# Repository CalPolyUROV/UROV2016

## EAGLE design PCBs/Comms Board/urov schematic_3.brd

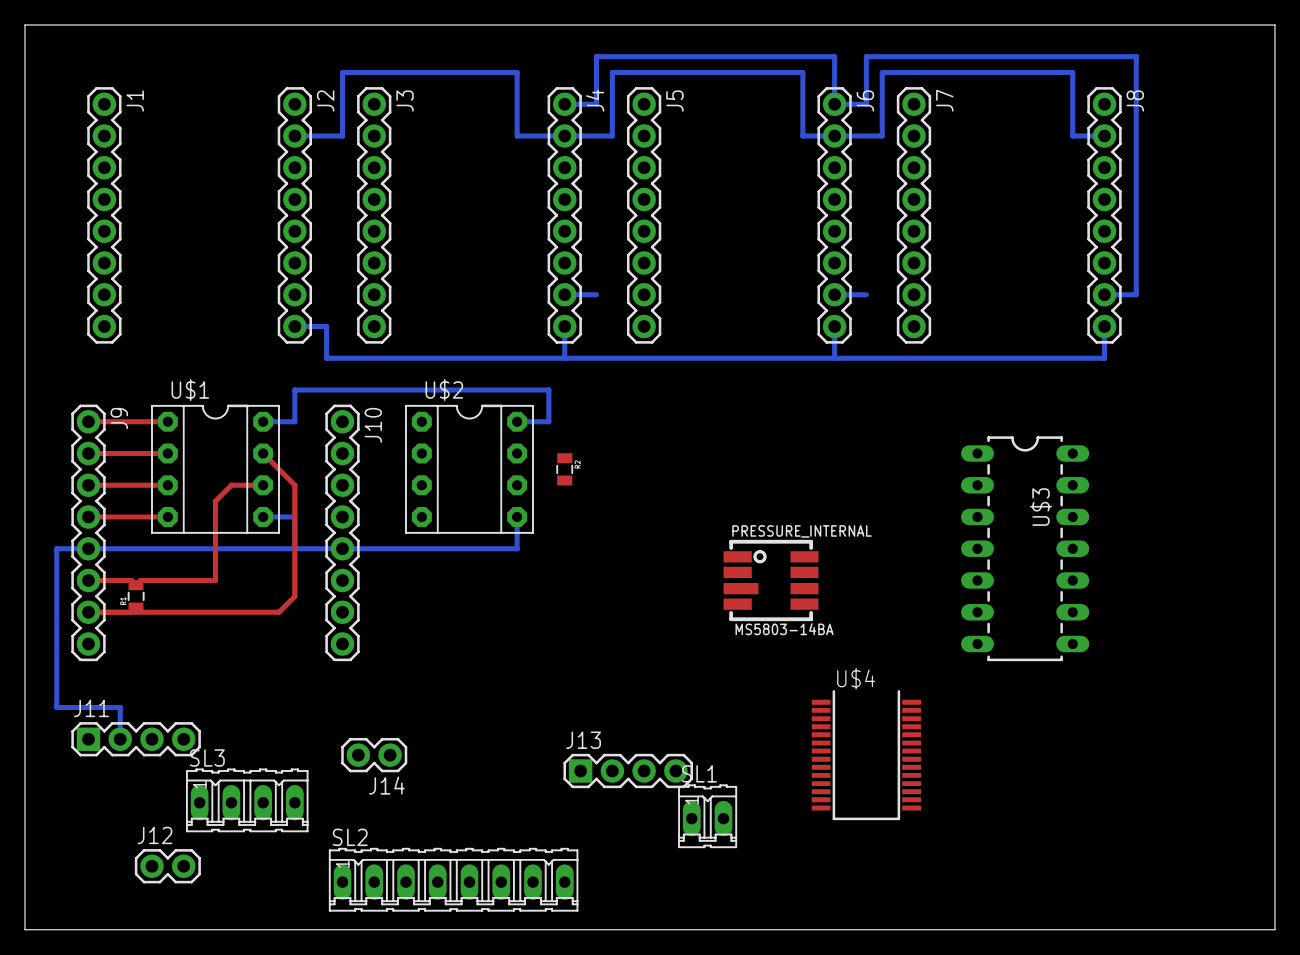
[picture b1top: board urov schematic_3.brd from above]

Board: 2 copper layers, 100.0 x 72.4 mm, 24 parts (0 on the bottom side), 21 nets.

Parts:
J1, J2, J3, J4, J5, J6, J7, J8, J9, J10: 1X08_ROUND
J11, J13: 1X04
J12, J14: 1X02
PRESSURE_INTERNAL: MS5803-14BA; MS5803
R1, R2: 120; 0805
SL1: 02P
SL2: 08P
SL3: 04P
U$1, U$2: MAX485DIL; DIL08
U$3: ATTINY84ATTINY84-20PU; DIL14
U$4: MAX4574A; 28-SSOP

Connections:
A_DIP8_1: J9.6, R1.2, U$1.6
A_DIP8_2: J10.6, R2.2, U$2.6
B_DIP8_1: J9.7, R1.1, U$1.7
B_DIP8_2: J10.7, R2.1, U$2.7
GND: J2.1, J2.7, J4.1, J4.7, J6.1, J6.7, J8.1, J8.7, J9.5, J10.5, J11.2, PRESSURE_INTERNAL.2, PRESSURE_INTERNAL.6, U$1.5, U$2.5
MISO: J13.3, PRESSURE_INTERNAL.8
MOSI: J12.1, J13.4, PRESSURE_INTERNAL.7
unnamed: J9.1, U$1.1
unnamed: J9.2, U$1.2
unnamed: J9.3, U$1.3
unnamed: J9.4, U$1.4
unnamed: J10.1, U$2.1
unnamed: J10.2, U$2.2
unnamed: J10.3, U$2.3
unnamed: J10.4, U$2.4
SCL: J11.4, J14.2, PRESSURE_INTERNAL.1
SCLK: J13.2, J14.1
SDA: J11.3, J12.2
SS: J13.1, PRESSURE_INTERNAL.3
VDD: J2.2, J4.2, J6.2, J8.2, J9.8, J10.8, U$1.8, U$2.8
VMOT: J2.8, J4.8, J6.8, J8.8

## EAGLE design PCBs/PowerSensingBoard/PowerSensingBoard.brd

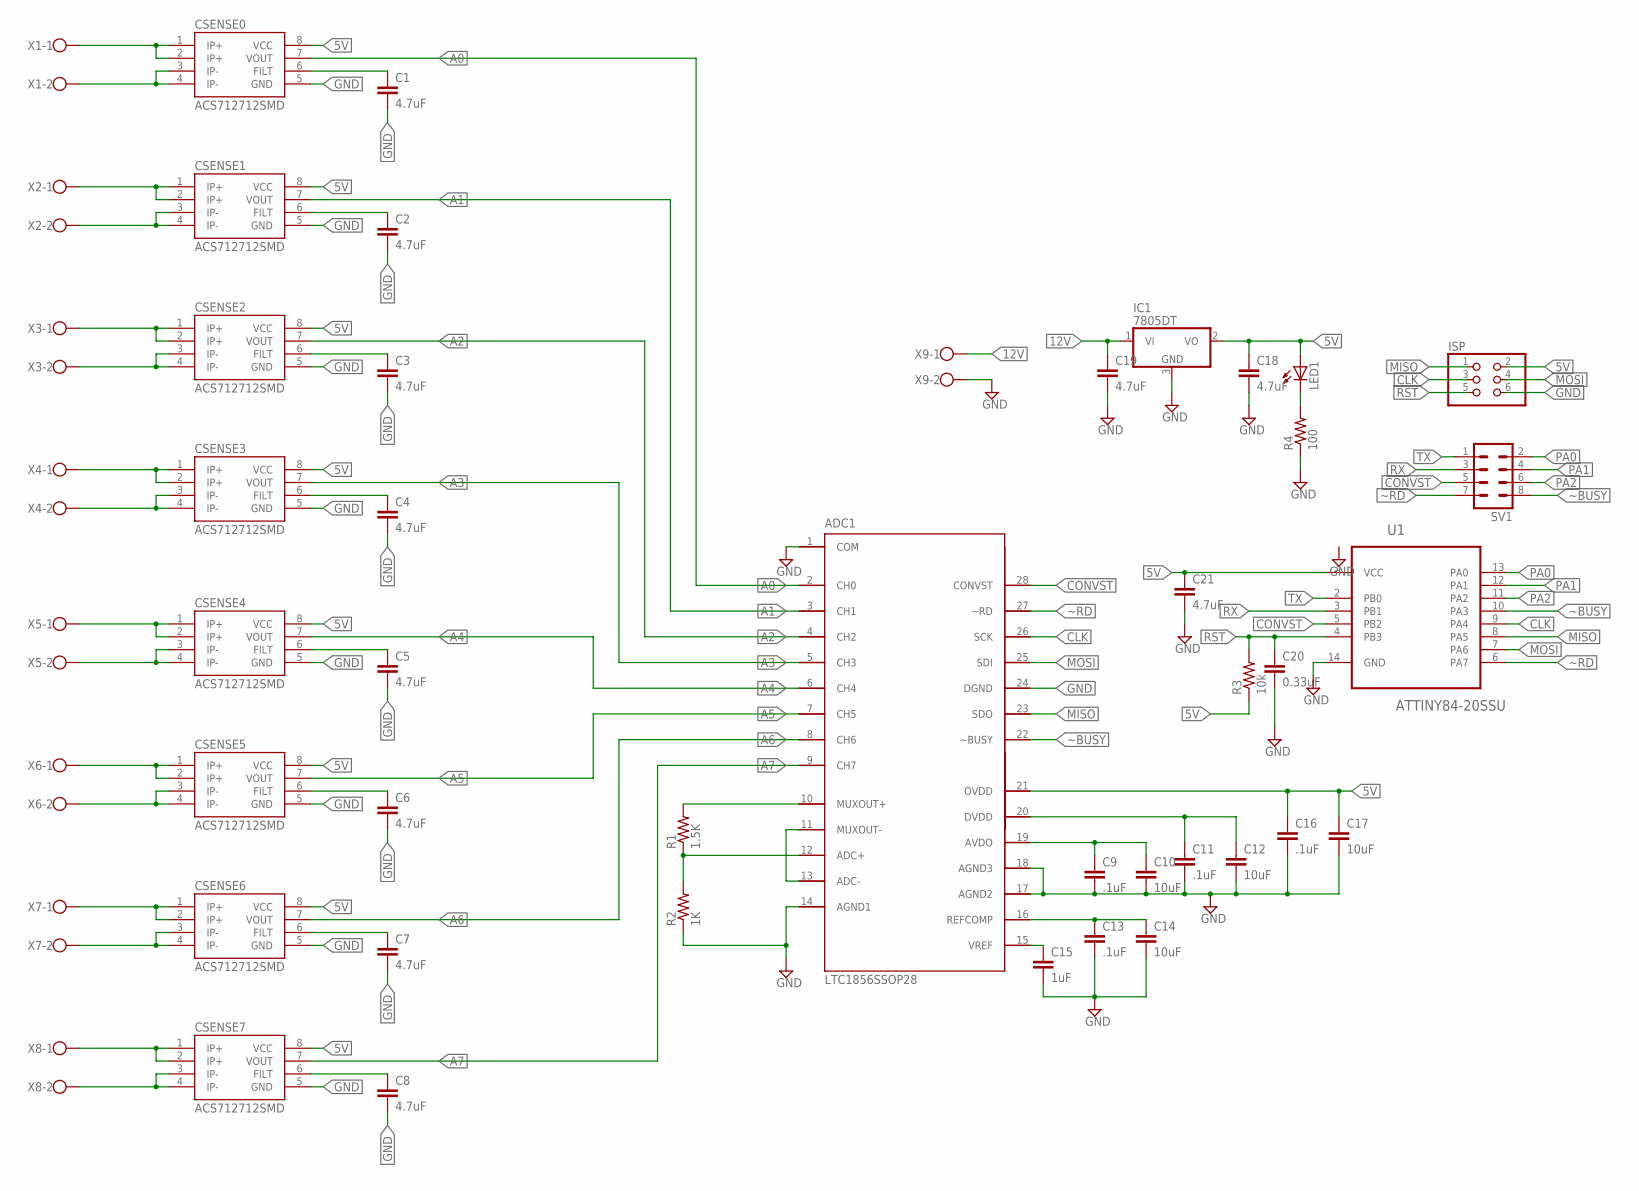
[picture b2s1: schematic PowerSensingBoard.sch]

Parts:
ADC1: LTC1856SSOP28; SSOP-28
C1, C2, C3, C4, C5, C6, C7, C8, C18, C19, C21: 4.7uF; 0603-CAP
C9, C11, C13, C16: .1uF; 0603-CAP
C10, C12, C14, C17: 10uF; 0603-CAP
C15: 1uF; 0603-CAP
C20: 0.33uF; 0805-CAP
CSENSE0, CSENSE1, CSENSE2, CSENSE3, CSENSE4, CSENSE5, CSENSE6, CSENSE7: ACS712712SMD; SO08
IC1: 7805DT; TO252
ISP: PINHD-2X3; 2X03
LED1: LEDCHIP-LED0805; CHIP-LED0805
R1: 1.5K; 0603-RES
R2: 1K; 0603-RES
R3: 10k; 0805
R4: 100; 0603-RES
SV1: MA04-2
U1: ATTINY84-20SSU; SOIC127P600X175-14N
X1, X2, X3, X4, X5, X6, X7, X8, X9: W237-102

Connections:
5V: ADC1.21 (OVDD), C16.1, C17.1, C18.1, C21.1, CSENSE0.8 (VCC), CSENSE1.8 (VCC), CSENSE2.8 (VCC), CSENSE3.8 (VCC), CSENSE4.8 (VCC), CSENSE5.8 (VCC), CSENSE6.8 (VCC), CSENSE7.8 (VCC), IC1.2 (VO), ISP.2, LED1.A, R3.1, U1.1 (VCC)
12V: C19.1, IC1.1 (VI), X9.1
A0: ADC1.2 (CH0), CSENSE0.7 (VOUT)
A1: ADC1.3 (CH1), CSENSE1.7 (VOUT)
A2: ADC1.4 (CH2), CSENSE2.7 (VOUT)
A3: ADC1.5 (CH3), CSENSE3.7 (VOUT)
A4: ADC1.6 (CH4), CSENSE4.7 (VOUT)
A5: ADC1.7 (CH5), CSENSE5.7 (VOUT)
A6: ADC1.8 (CH6), CSENSE6.7 (VOUT)
A7: ADC1.9 (CH7), CSENSE7.7 (VOUT)
CLK: ADC1.26 (SCK), ISP.3, U1.9 (PA4)
CONVST: ADC1.28 (CONVST), SV1.5, U1.5 (PB2)
FILT1: C1.1, CSENSE0.6 (FILT)
FILT2: C2.1, CSENSE1.6 (FILT)
FILT3: C3.1, CSENSE2.6 (FILT)
FILT4: C4.1, CSENSE3.6 (FILT)
FILT5: C5.1, CSENSE4.6 (FILT)
FILT6: C6.1, CSENSE5.6 (FILT)
FILT7: C7.1, CSENSE6.6 (FILT)
FILT8: C8.1, CSENSE7.6 (FILT)
GND: ADC1.1 (COM), ADC1.14 (AGND1), ADC1.17 (AGND2), ADC1.18 (AGND3), ADC1.24 (DGND), C1.2, C2.2, C3.2, C4.2, C5.2, C6.2, C7.2, C8.2, C9.2, C10.2, C11.2, C12.2, C13.2, C14.2, C15.2, C16.2, C17.2, C18.2, C19.2, C20.2, C21.2, CSENSE0.5 (GND), CSENSE1.5 (GND), CSENSE2.5 (GND), CSENSE3.5 (GND), CSENSE4.5 (GND), CSENSE5.5 (GND), CSENSE6.5 (GND), CSENSE7.5 (GND), IC1.3 (GND), ISP.6, R2.1, R4.1, U1.14 (GND), X9.2
INT1: CSENSE0.1 (IP+), CSENSE0.2 (IP+), X1.1
INT2: CSENSE1.1 (IP+), CSENSE1.2 (IP+), X2.1
INT3: CSENSE2.1 (IP+), CSENSE2.2 (IP+), X3.1
INT4: CSENSE3.1 (IP+), CSENSE3.2 (IP+), X4.1
INT5: CSENSE4.1 (IP+), CSENSE4.2 (IP+), X5.1
INT6: CSENSE5.1 (IP+), CSENSE5.2 (IP+), X6.1
INT7: CSENSE6.1 (IP+), CSENSE6.2 (IP+), X7.1
INT8: CSENSE7.1 (IP+), CSENSE7.2 (IP+), X8.1
LED1: LED1.C, R4.2
MISO: ADC1.23 (SDO), ISP.1, U1.8 (PA5)
MOSI: ADC1.25 (SDI), ISP.4, U1.7 (PA6)
MUXOUT+: ADC1.10 (MUXOUT+), R1.2
MUXOUT-: ADC1.12 (ADC+), R1.1, R2.2
unnamed: ADC1.11 (MUXOUT-), ADC1.13 (ADC-)
unnamed: ADC1.20 (DVDD), C11.1, C12.1
unnamed: ADC1.19 (AVDO), C9.1, C10.1
unnamed: ADC1.15 (VREF), C15.1
unnamed: ADC1.16 (REFCOMP), C13.1, C14.1
OUTT1: CSENSE0.3 (IP-), CSENSE0.4 (IP-), X1.2
OUTT2: CSENSE1.3 (IP-), CSENSE1.4 (IP-), X2.2
OUTT3: CSENSE2.3 (IP-), CSENSE2.4 (IP-), X3.2
OUTT4: CSENSE3.3 (IP-), CSENSE3.4 (IP-), X4.2
OUTT5: CSENSE4.3 (IP-), CSENSE4.4 (IP-), X5.2
OUTT6: CSENSE5.3 (IP-), CSENSE5.4 (IP-), X6.2
OUTT7: CSENSE6.3 (IP-), CSENSE6.4 (IP-), X7.2
OUTT8: CSENSE7.3 (IP-), CSENSE7.4 (IP-), X8.2
PA0: SV1.2, U1.13 (PA0)
PA1: SV1.4, U1.12 (PA1)
PA2: SV1.6, U1.11 (PA2)
RST: C20.1, ISP.5, R3.2, U1.4 (PB3)
RX: SV1.3, U1.3 (PB1)
TX: SV1.1, U1.2 (PB0)
~BUSY: ADC1.22 (~BUSY), SV1.8, U1.10 (PA3)
~RD: ADC1.27 (~RD), SV1.7, U1.6 (PA7)

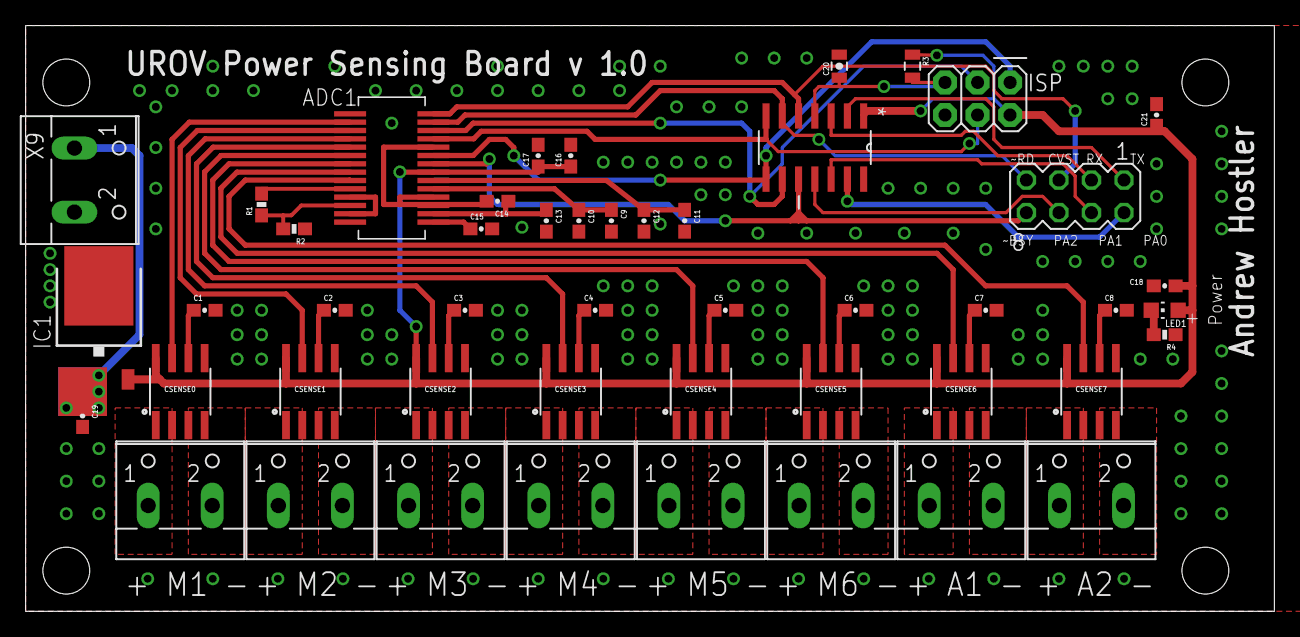
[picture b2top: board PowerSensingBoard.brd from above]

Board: 2 copper layers, 97.5 x 45.7 mm, 48 parts (0 on the bottom side), 55 nets.

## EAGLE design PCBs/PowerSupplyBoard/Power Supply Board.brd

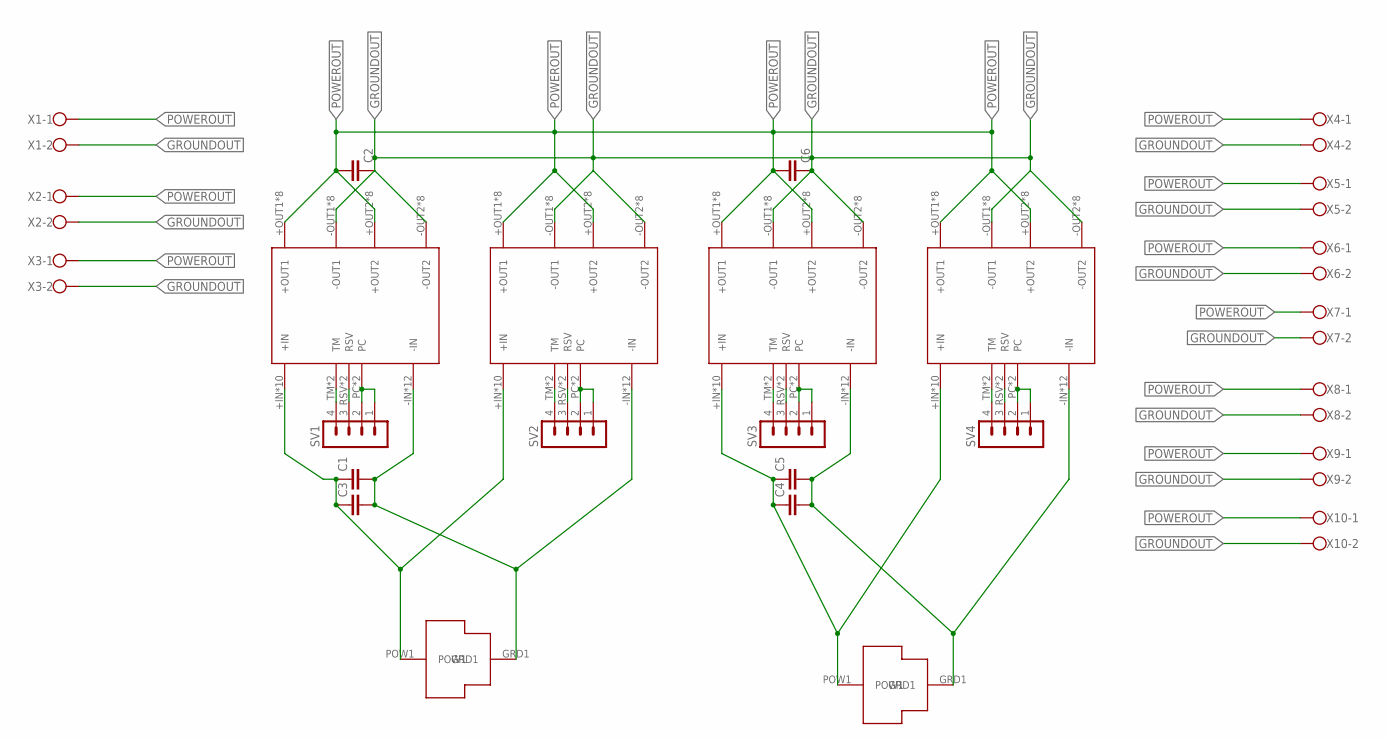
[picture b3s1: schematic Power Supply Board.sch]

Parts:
C1, C2, C3, C4, C5, C6: C2,5-3; C2.5-3
SV1, SV2, SV3, SV4: MA04-1
U$3, U$9: MOLEXMEGAFIT
VC1, VC2, VC3, VC4: VOLTAGECONVERTER
X1, X2, X3, X4, X5, X6, X7, X8, X9, X10: W237-102

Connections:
GROUNDIN: C1.2, C3.2, C4.2, C5.2, U$3.GRD1, U$9.GRD1, VC1.-IN, VC1.-IN@0 (-IN), VC1.-IN@1 (-IN), VC1.-IN@2 (-IN), VC1.-IN@3 (-IN), VC1.-IN@4 (-IN), VC1.-IN@5 (-IN), VC1.-IN@6 (-IN), VC1.-IN@7 (-IN), VC1.-IN@8 (-IN), VC1.-IN@9 (-IN), VC1.-IN@10 (-IN), VC2.-IN, VC2.-IN@0 (-IN), VC2.-IN@1 (-IN), VC2.-IN@2 (-IN), VC2.-IN@3 (-IN), VC2.-IN@4 (-IN), VC2.-IN@5 (-IN), VC2.-IN@6 (-IN), VC2.-IN@7 (-IN), VC2.-IN@8 (-IN), VC2.-IN@9 (-IN), VC2.-IN@10 (-IN), VC3.-IN, VC3.-IN@0 (-IN), VC3.-IN@1 (-IN), VC3.-IN@2 (-IN), VC3.-IN@3 (-IN), VC3.-IN@4 (-IN), VC3.-IN@5 (-IN), VC3.-IN@6 (-IN), VC3.-IN@7 (-IN), VC3.-IN@8 (-IN), VC3.-IN@9 (-IN), VC3.-IN@10 (-IN), VC4.-IN, VC4.-IN@0 (-IN), VC4.-IN@1 (-IN), VC4.-IN@2 (-IN), VC4.-IN@3 (-IN), VC4.-IN@4 (-IN), VC4.-IN@5 (-IN), VC4.-IN@6 (-IN), VC4.-IN@7 (-IN), VC4.-IN@8 (-IN), VC4.-IN@9 (-IN), VC4.-IN@10 (-IN)
GROUNDOUT: C2.1, C6.1, VC1.-OUT1, VC1.-OUT1@1 (-OUT1), VC1.-OUT1@2 (-OUT1), VC1.-OUT1@3 (-OUT1), VC1.-OUT1@4 (-OUT1), VC1.-OUT1@5 (-OUT1), VC1.-OUT1@6 (-OUT1), VC1.-OUT1@7 (-OUT1), VC1.-OUT2, VC1.-OUT2@1 (-OUT2), VC1.-OUT2@2 (-OUT2), VC1.-OUT2@3 (-OUT2), VC1.-OUT2@4 (-OUT2), VC1.-OUT2@5 (-OUT2), VC1.-OUT2@6 (-OUT2), VC1.-OUT2@7 (-OUT2), VC2.-OUT1, VC2.-OUT1@1 (-OUT1), VC2.-OUT1@2 (-OUT1), VC2.-OUT1@3 (-OUT1), VC2.-OUT1@4 (-OUT1), VC2.-OUT1@5 (-OUT1), VC2.-OUT1@6 (-OUT1), VC2.-OUT1@7 (-OUT1), VC2.-OUT2, VC2.-OUT2@1 (-OUT2), VC2.-OUT2@2 (-OUT2), VC2.-OUT2@3 (-OUT2), VC2.-OUT2@4 (-OUT2), VC2.-OUT2@5 (-OUT2), VC2.-OUT2@6 (-OUT2), VC2.-OUT2@7 (-OUT2), VC3.-OUT1, VC3.-OUT1@1 (-OUT1), VC3.-OUT1@2 (-OUT1), VC3.-OUT1@3 (-OUT1), VC3.-OUT1@4 (-OUT1), VC3.-OUT1@5 (-OUT1), VC3.-OUT1@6 (-OUT1), VC3.-OUT1@7 (-OUT1), VC3.-OUT2, VC3.-OUT2@1 (-OUT2), VC3.-OUT2@2 (-OUT2), VC3.-OUT2@3 (-OUT2), VC3.-OUT2@4 (-OUT2), VC3.-OUT2@5 (-OUT2), VC3.-OUT2@6 (-OUT2), VC3.-OUT2@7 (-OUT2), VC4.-OUT1, VC4.-OUT1@1 (-OUT1), VC4.-OUT1@2 (-OUT1), VC4.-OUT1@3 (-OUT1), VC4.-OUT1@4 (-OUT1), VC4.-OUT1@5 (-OUT1), VC4.-OUT1@6 (-OUT1), VC4.-OUT1@7 (-OUT1), VC4.-OUT2, VC4.-OUT2@1 (-OUT2), VC4.-OUT2@2 (-OUT2), VC4.-OUT2@3 (-OUT2), VC4.-OUT2@4 (-OUT2), VC4.-OUT2@5 (-OUT2), VC4.-OUT2@6 (-OUT2), VC4.-OUT2@7 (-OUT2), X1.2, X2.2, X3.2, X4.2, X5.2, X6.2, X7.2, X8.2, X9.2, X10.2
unnamed: SV1.3, VC1.RSV, VC1.RSV@1 (RSV)
unnamed: SV2.3, VC2.RSV, VC2.RSV@1 (RSV)
unnamed: SV3.3, VC3.RSV, VC3.RSV@1 (RSV)
unnamed: SV4.3, VC4.RSV, VC4.RSV@1 (RSV)
PC1: SV1.1, SV1.2, VC1.PC, VC1.PC21 (PC)
PC2: SV2.1, SV2.2, VC2.PC, VC2.PC21 (PC)
PC3: SV3.1, SV3.2, VC3.PC, VC3.PC21 (PC)
PC4: SV4.1, SV4.2, VC4.PC, VC4.PC21 (PC)
POWERIN12: C1.1, C3.1, U$3.POW1, VC1.+IN, VC1.+IN@1 (+IN), VC1.+IN@2 (+IN), VC1.+IN@3 (+IN), VC1.+IN@4 (+IN), VC1.+IN@5 (+IN), VC1.+IN@6 (+IN), VC1.+IN@7 (+IN), VC1.+IN@8 (+IN), VC1.+IN@9 (+IN), VC2.+IN, VC2.+IN@1 (+IN), VC2.+IN@2 (+IN), VC2.+IN@3 (+IN), VC2.+IN@4 (+IN), VC2.+IN@5 (+IN), VC2.+IN@6 (+IN), VC2.+IN@7 (+IN), VC2.+IN@8 (+IN), VC2.+IN@9 (+IN)
POWERIN34: C4.1, C5.1, U$9.POW1, VC3.+IN, VC3.+IN@1 (+IN), VC3.+IN@2 (+IN), VC3.+IN@3 (+IN), VC3.+IN@4 (+IN), VC3.+IN@5 (+IN), VC3.+IN@6 (+IN), VC3.+IN@7 (+IN), VC3.+IN@8 (+IN), VC3.+IN@9 (+IN), VC4.+IN, VC4.+IN@1 (+IN), VC4.+IN@2 (+IN), VC4.+IN@3 (+IN), VC4.+IN@4 (+IN), VC4.+IN@5 (+IN), VC4.+IN@6 (+IN), VC4.+IN@7 (+IN), VC4.+IN@8 (+IN), VC4.+IN@9 (+IN)
POWEROUT: C2.2, C6.2, VC1.+OUT1, VC1.+OUT1@1 (+OUT1), VC1.+OUT1@2 (+OUT1), VC1.+OUT1@3 (+OUT1), VC1.+OUT1@4 (+OUT1), VC1.+OUT1@5 (+OUT1), VC1.+OUT1@6 (+OUT1), VC1.+OUT1@7 (+OUT1), VC1.+OUT2, VC1.+OUT2@1 (+OUT2), VC1.+OUT2@2 (+OUT2), VC1.+OUT2@3 (+OUT2), VC1.+OUT2@4 (+OUT2), VC1.+OUT2@5 (+OUT2), VC1.+OUT2@6 (+OUT2), VC1.+OUT2@7 (+OUT2), VC2.+OUT1, VC2.+OUT1@1 (+OUT1), VC2.+OUT1@2 (+OUT1), VC2.+OUT1@3 (+OUT1), VC2.+OUT1@4 (+OUT1), VC2.+OUT1@5 (+OUT1), VC2.+OUT1@6 (+OUT1), VC2.+OUT1@7 (+OUT1), VC2.+OUT2, VC2.+OUT2@1 (+OUT2), VC2.+OUT2@2 (+OUT2), VC2.+OUT2@3 (+OUT2), VC2.+OUT2@4 (+OUT2), VC2.+OUT2@5 (+OUT2), VC2.+OUT2@6 (+OUT2), VC2.+OUT2@7 (+OUT2), VC3.+OUT1, VC3.+OUT1@1 (+OUT1), VC3.+OUT1@2 (+OUT1), VC3.+OUT1@3 (+OUT1), VC3.+OUT1@4 (+OUT1), VC3.+OUT1@5 (+OUT1), VC3.+OUT1@6 (+OUT1), VC3.+OUT1@7 (+OUT1), VC3.+OUT2, VC3.+OUT2@1 (+OUT2), VC3.+OUT2@2 (+OUT2), VC3.+OUT2@3 (+OUT2), VC3.+OUT2@4 (+OUT2), VC3.+OUT2@5 (+OUT2), VC3.+OUT2@6 (+OUT2), VC3.+OUT2@7 (+OUT2), VC4.+OUT1, VC4.+OUT1@1 (+OUT1), VC4.+OUT1@2 (+OUT1), VC4.+OUT1@3 (+OUT1), VC4.+OUT1@4 (+OUT1), VC4.+OUT1@5 (+OUT1), VC4.+OUT1@6 (+OUT1), VC4.+OUT1@7 (+OUT1), VC4.+OUT2, VC4.+OUT2@1 (+OUT2), VC4.+OUT2@2 (+OUT2), VC4.+OUT2@3 (+OUT2), VC4.+OUT2@4 (+OUT2), VC4.+OUT2@5 (+OUT2), VC4.+OUT2@6 (+OUT2), VC4.+OUT2@7 (+OUT2), X1.1, X2.1, X3.1, X4.1, X5.1, X6.1, X7.1, X8.1, X9.1, X10.1
TM1: SV1.4, VC1.TM, VC1.TM@1 (TM)
TM2: SV2.4, VC2.TM, VC2.TM@1 (TM)
TM3: SV3.4, VC3.TM, VC3.TM@1 (TM)
TM4: SV4.4, VC4.TM, VC4.TM@1 (TM)

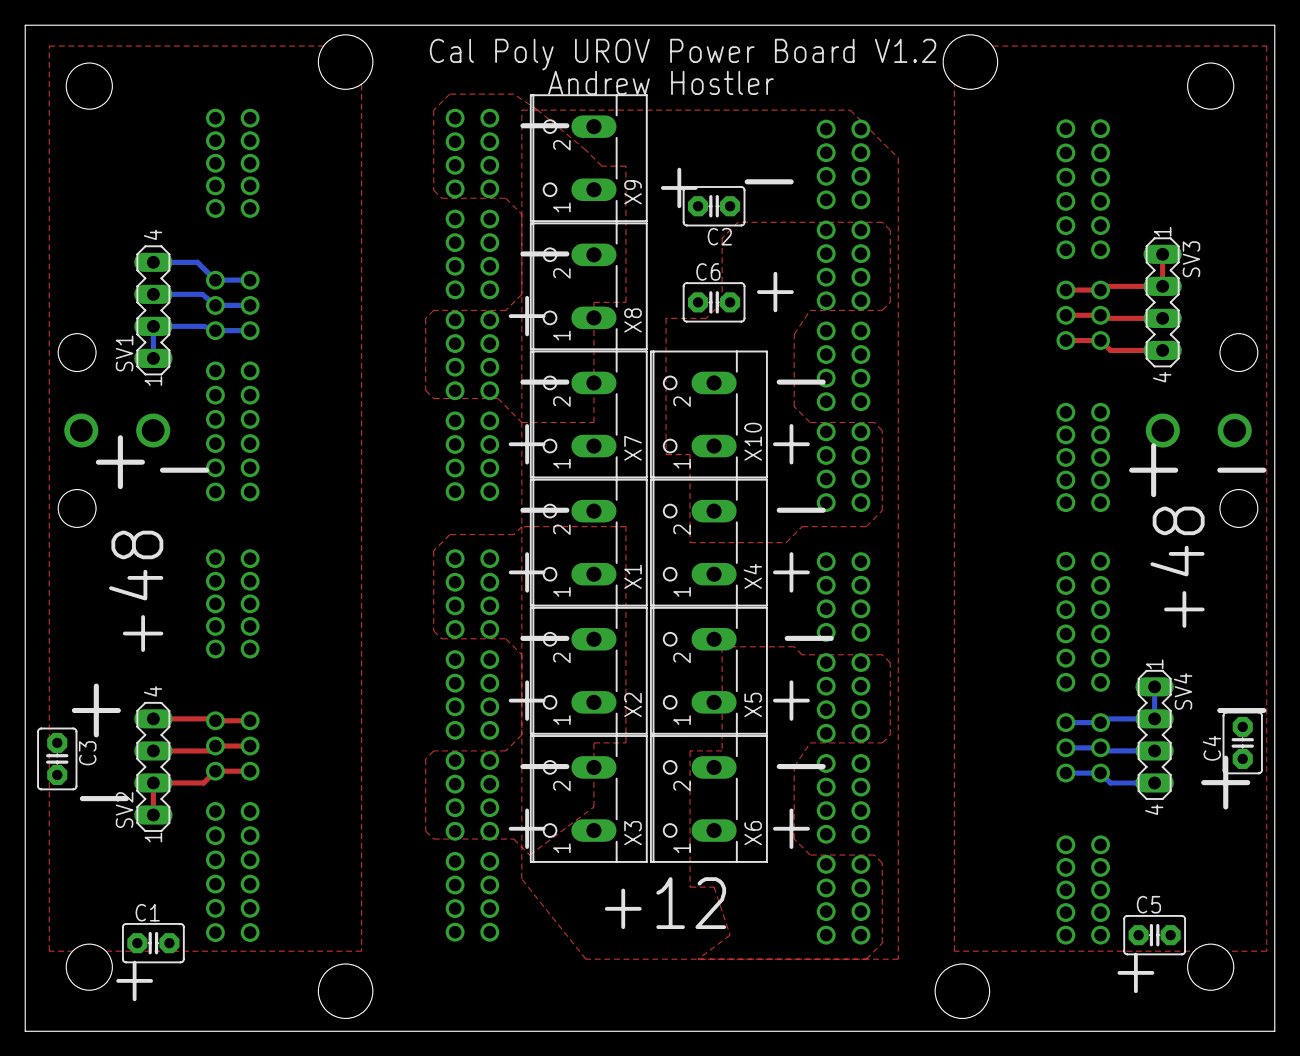
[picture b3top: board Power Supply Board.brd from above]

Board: 2 copper layers, 99.1 x 79.8 mm, 26 parts (0 on the bottom side), 17 nets.

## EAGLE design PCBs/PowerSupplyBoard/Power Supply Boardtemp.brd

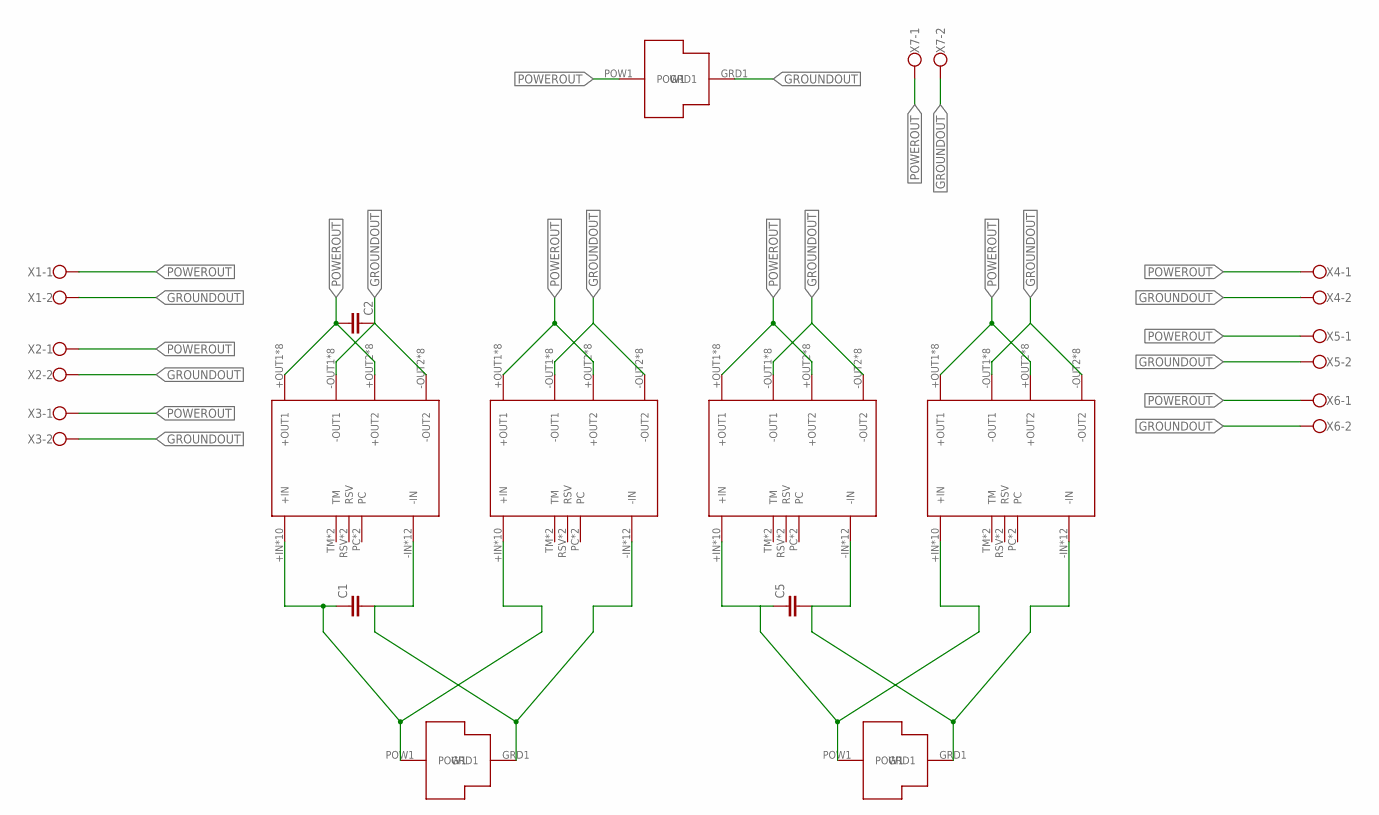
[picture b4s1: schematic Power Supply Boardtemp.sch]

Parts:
C1, C2, C5: C2,5-3; C2.5-3
U$2, U$3, U$9: MOLEXMEGAFIT
VC1, VC2, VC3, VC4: VOLTAGECONVERTER
X1, X2, X3, X4, X5, X6, X7: W237-102

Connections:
GROUNDIN: C1.2, C5.2, U$3.GRD1, U$9.GRD1, VC1.-IN, VC1.-IN@0 (-IN), VC1.-IN@1 (-IN), VC1.-IN@2 (-IN), VC1.-IN@3 (-IN), VC1.-IN@4 (-IN), VC1.-IN@5 (-IN), VC1.-IN@6 (-IN), VC1.-IN@7 (-IN), VC1.-IN@8 (-IN), VC1.-IN@9 (-IN), VC1.-IN@10 (-IN), VC2.-IN, VC2.-IN@0 (-IN), VC2.-IN@1 (-IN), VC2.-IN@2 (-IN), VC2.-IN@3 (-IN), VC2.-IN@4 (-IN), VC2.-IN@5 (-IN), VC2.-IN@6 (-IN), VC2.-IN@7 (-IN), VC2.-IN@8 (-IN), VC2.-IN@9 (-IN), VC2.-IN@10 (-IN), VC3.-IN, VC3.-IN@0 (-IN), VC3.-IN@1 (-IN), VC3.-IN@2 (-IN), VC3.-IN@3 (-IN), VC3.-IN@4 (-IN), VC3.-IN@5 (-IN), VC3.-IN@6 (-IN), VC3.-IN@7 (-IN), VC3.-IN@8 (-IN), VC3.-IN@9 (-IN), VC3.-IN@10 (-IN), VC4.-IN, VC4.-IN@0 (-IN), VC4.-IN@1 (-IN), VC4.-IN@2 (-IN), VC4.-IN@3 (-IN), VC4.-IN@4 (-IN), VC4.-IN@5 (-IN), VC4.-IN@6 (-IN), VC4.-IN@7 (-IN), VC4.-IN@8 (-IN), VC4.-IN@9 (-IN), VC4.-IN@10 (-IN)
GROUNDOUT: C2.1, U$2.GRD1, VC1.-OUT1, VC1.-OUT1@1 (-OUT1), VC1.-OUT1@2 (-OUT1), VC1.-OUT1@3 (-OUT1), VC1.-OUT1@4 (-OUT1), VC1.-OUT1@5 (-OUT1), VC1.-OUT1@6 (-OUT1), VC1.-OUT1@7 (-OUT1), VC1.-OUT2, VC1.-OUT2@1 (-OUT2), VC1.-OUT2@2 (-OUT2), VC1.-OUT2@3 (-OUT2), VC1.-OUT2@4 (-OUT2), VC1.-OUT2@5 (-OUT2), VC1.-OUT2@6 (-OUT2), VC1.-OUT2@7 (-OUT2), VC2.-OUT1, VC2.-OUT1@1 (-OUT1), VC2.-OUT1@2 (-OUT1), VC2.-OUT1@3 (-OUT1), VC2.-OUT1@4 (-OUT1), VC2.-OUT1@5 (-OUT1), VC2.-OUT1@6 (-OUT1), VC2.-OUT1@7 (-OUT1), VC2.-OUT2, VC2.-OUT2@1 (-OUT2), VC2.-OUT2@2 (-OUT2), VC2.-OUT2@3 (-OUT2), VC2.-OUT2@4 (-OUT2), VC2.-OUT2@5 (-OUT2), VC2.-OUT2@6 (-OUT2), VC2.-OUT2@7 (-OUT2), VC3.-OUT1, VC3.-OUT1@1 (-OUT1), VC3.-OUT1@2 (-OUT1), VC3.-OUT1@3 (-OUT1), VC3.-OUT1@4 (-OUT1), VC3.-OUT1@5 (-OUT1), VC3.-OUT1@6 (-OUT1), VC3.-OUT1@7 (-OUT1), VC3.-OUT2, VC3.-OUT2@1 (-OUT2), VC3.-OUT2@2 (-OUT2), VC3.-OUT2@3 (-OUT2), VC3.-OUT2@4 (-OUT2), VC3.-OUT2@5 (-OUT2), VC3.-OUT2@6 (-OUT2), VC3.-OUT2@7 (-OUT2), VC4.-OUT1, VC4.-OUT1@1 (-OUT1), VC4.-OUT1@2 (-OUT1), VC4.-OUT1@3 (-OUT1), VC4.-OUT1@4 (-OUT1), VC4.-OUT1@5 (-OUT1), VC4.-OUT1@6 (-OUT1), VC4.-OUT1@7 (-OUT1), VC4.-OUT2, VC4.-OUT2@1 (-OUT2), VC4.-OUT2@2 (-OUT2), VC4.-OUT2@3 (-OUT2), VC4.-OUT2@4 (-OUT2), VC4.-OUT2@5 (-OUT2), VC4.-OUT2@6 (-OUT2), VC4.-OUT2@7 (-OUT2), X1.2, X2.2, X3.2, X4.2, X5.2, X6.2, X7.2
POWERIN12: C1.1, U$3.POW1, VC1.+IN, VC1.+IN@1 (+IN), VC1.+IN@2 (+IN), VC1.+IN@3 (+IN), VC1.+IN@4 (+IN), VC1.+IN@5 (+IN), VC1.+IN@6 (+IN), VC1.+IN@7 (+IN), VC1.+IN@8 (+IN), VC1.+IN@9 (+IN), VC2.+IN, VC2.+IN@1 (+IN), VC2.+IN@2 (+IN), VC2.+IN@3 (+IN), VC2.+IN@4 (+IN), VC2.+IN@5 (+IN), VC2.+IN@6 (+IN), VC2.+IN@7 (+IN), VC2.+IN@8 (+IN), VC2.+IN@9 (+IN)
POWERIN34: C5.1, U$9.POW1, VC3.+IN, VC3.+IN@1 (+IN), VC3.+IN@2 (+IN), VC3.+IN@3 (+IN), VC3.+IN@4 (+IN), VC3.+IN@5 (+IN), VC3.+IN@6 (+IN), VC3.+IN@7 (+IN), VC3.+IN@8 (+IN), VC3.+IN@9 (+IN), VC4.+IN, VC4.+IN@1 (+IN), VC4.+IN@2 (+IN), VC4.+IN@3 (+IN), VC4.+IN@4 (+IN), VC4.+IN@5 (+IN), VC4.+IN@6 (+IN), VC4.+IN@7 (+IN), VC4.+IN@8 (+IN), VC4.+IN@9 (+IN)
POWEROUT: C2.2, U$2.POW1, VC1.+OUT1, VC1.+OUT1@1 (+OUT1), VC1.+OUT1@2 (+OUT1), VC1.+OUT1@3 (+OUT1), VC1.+OUT1@4 (+OUT1), VC1.+OUT1@5 (+OUT1), VC1.+OUT1@6 (+OUT1), VC1.+OUT1@7 (+OUT1), VC1.+OUT2, VC1.+OUT2@1 (+OUT2), VC1.+OUT2@2 (+OUT2), VC1.+OUT2@3 (+OUT2), VC1.+OUT2@4 (+OUT2), VC1.+OUT2@5 (+OUT2), VC1.+OUT2@6 (+OUT2), VC1.+OUT2@7 (+OUT2), VC2.+OUT1, VC2.+OUT1@1 (+OUT1), VC2.+OUT1@2 (+OUT1), VC2.+OUT1@3 (+OUT1), VC2.+OUT1@4 (+OUT1), VC2.+OUT1@5 (+OUT1), VC2.+OUT1@6 (+OUT1), VC2.+OUT1@7 (+OUT1), VC2.+OUT2, VC2.+OUT2@1 (+OUT2), VC2.+OUT2@2 (+OUT2), VC2.+OUT2@3 (+OUT2), VC2.+OUT2@4 (+OUT2), VC2.+OUT2@5 (+OUT2), VC2.+OUT2@6 (+OUT2), VC2.+OUT2@7 (+OUT2), VC3.+OUT1, VC3.+OUT1@1 (+OUT1), VC3.+OUT1@2 (+OUT1), VC3.+OUT1@3 (+OUT1), VC3.+OUT1@4 (+OUT1), VC3.+OUT1@5 (+OUT1), VC3.+OUT1@6 (+OUT1), VC3.+OUT1@7 (+OUT1), VC3.+OUT2, VC3.+OUT2@1 (+OUT2), VC3.+OUT2@2 (+OUT2), VC3.+OUT2@3 (+OUT2), VC3.+OUT2@4 (+OUT2), VC3.+OUT2@5 (+OUT2), VC3.+OUT2@6 (+OUT2), VC3.+OUT2@7 (+OUT2), VC4.+OUT1, VC4.+OUT1@1 (+OUT1), VC4.+OUT1@2 (+OUT1), VC4.+OUT1@3 (+OUT1), VC4.+OUT1@4 (+OUT1), VC4.+OUT1@5 (+OUT1), VC4.+OUT1@6 (+OUT1), VC4.+OUT1@7 (+OUT1), VC4.+OUT2, VC4.+OUT2@1 (+OUT2), VC4.+OUT2@2 (+OUT2), VC4.+OUT2@3 (+OUT2), VC4.+OUT2@4 (+OUT2), VC4.+OUT2@5 (+OUT2), VC4.+OUT2@6 (+OUT2), VC4.+OUT2@7 (+OUT2), X1.1, X2.1, X3.1, X4.1, X5.1, X6.1, X7.1

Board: 2 copper layers, 24 parts (0 on the bottom side), 5 nets, no tracks yet.

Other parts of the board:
E$1, E$2, E$3, E$4, E$5, E$6, E$7: W237-102

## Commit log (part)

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2015-10-02 Added last year's code
    We will probably reuse parts of this, but definitely revamp a lot as
    well.
    Communications needed a makeover.
2015-10-02 Adding Jonathan's Code
    Jonathan figured out some RS485 comms stuff this week, adding it for
    others to use.
2015-10-05 Oct 3rd update
    Some new progress on the communications testing by Jonathan and Tina
2015-10-05 Readme
    Added real readme file… more to be added later
2015-10-05 Updated code to control the motors of Santiago and to function on the Arduino Mega with 3 serial ports
2015-10-05 Added instructions for installing current dependiencies
2015-10-05 Added new folders
    Each new folder has a readme file for use to share notes in. When you
    guys start trying new sensors on your Arduino UNOs put the code in
    these. We can merge them with the core code of the Arduino mega later.
2015-10-10 Added Power Monitor for measuring Voltage stepped down from 48 V. - Anuj
2015-10-10 Create PressureSensorHardCoded
    Using the data sheet, hard coded the values.
2015-10-11 Added more comments
2015-10-12 Added useful references, moved a few files
    Hopefully this helps keep things organized :)
2015-10-14 fixed waitForStart to wait for a start signal
2015-10-14 added two way communication on an uno on a separate file, will remerge when I have a mega to double check with, also added system compatability, it should work with both linux and windows now, I will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
2015-10-15 moved gui into rs485 testing because that is where it should be
2015-10-16 improved the communication code for the gui, fixed issue with double blocking by adding timeout to reads
2015-10-17 quick save
2015-10-17 Create MS5541_Oct17_Working
    MS5541 Arduino, functional pressure and temperature sensor
    to do maybe:
    modulize
    callibrate
    waterproof
2015-10-18 Jonathan's Changes from Andrew's computer
    this is whatever he was up to for the last hour of build day Oct 17
2015-10-20 Fixed two way rs485 communication on serial ports.
2015-10-21 cleaned up the files in rs485_testing
2015-10-21 Added stepper motor resources
    Hopefully this helps. Stepper motors will be useful for external tools
    on the bot.
2015-10-22 added files that should have been there
2015-10-24 changed the structure of the files around
2015-10-25 work done during build time
2015-10-25 fixed pin and clock issues for the pressure sensor
2015-10-25 Oct 24 Update
    Added useful comments and links in stepper motors and TwoWayCom
2015-10-25 Added comments to functional
    Jonathan please read
2015-10-25 updated pin reference in Arduino.ino and and condensed input debugging
2015-10-25 updated pins to match mega rather than uno for the pressure.cpp
2015-10-26 Comments
    Comments updated for current sense
2015-10-26 large update to gui and communications associated with it
2015-10-26 fix merge?
2015-10-26 Revert "fix merge?"
    This reverts commit e8da7b3eed5a88db991e8e0ecd1c7a0840162b99.
2015-10-26 Create Stepper_Motor_Oct24
2015-10-29 Create TimedInterrupt_Example
    Read comments at beginning.
    This file is just an example of timer interrupt function
2015-10-30 Update TimedInterrupt_Example
    Working but stepper motor driver might be burned out.
    (inputs are good, smoke did not come out, but the 4 output wires that go to the stepper motor are not good. They stay at 8v and 0v
2015-10-31 Update and rename TimedInterrupt_Example to StepperMotor_Oct31
    Includes Timed Interrupting Stepper Motor, Timer 1 and Timer 2.
    Has input parameters
    Second half of intro comment section is outdated
2015-10-31 added accelerometer functionality
2015-10-31 Update StepperMotor_Oct31
2015-10-31 Update and rename Stepper_Motor_Oct24 to stepperMotor_cpp
    Use this as cpp
2015-10-31 Create stepperMotor_h
    use as .h
    4 functions:
    two for setting pins
    two for driving the stepper motor
2015-10-31 Update stepperMotor_h
2015-10-31 Update stepperMotor_cpp
2015-10-31 Update and rename StepperMotor_Oct31 to StepperMotor_TestFile_ino
2015-10-31 Update StepperMotor_TestFile_ino
2015-11-01 Update stepperMotor_h
    commented on some things I can add.
    ("Eric's To Do List")
2015-11-02 Update stepperMotor_h
    lines 11 through 56 are a summary of how I tested the run time of ISR.
    Conclusion starts line 41.
    Theoretically, each interrupt will take up to 8us.
    At a realistic speed of 30degrees/second, running the stepper motor slows other processes by 0.026667%.
    Extreme case: When microstepping at 1/16 steps and still going 30 degrees/second, running the stepper motor slows other processes by 0.4266667%
2015-11-06 Edits on old quad motors.cpp
    No real changes
2015-11-07 added accelerometer raw data.
2015-11-07 fixed some pressure sensor things.
2015-11-07 Create ComsMasterArd
2015-11-07 Create ComsSlaveArd
2015-11-07 added words
2015-11-08 Rename ComsMasterArd to SecondaryArduino/ComsMasterArd
2015-11-08 Update ComsMasterArd
2015-11-08 Rename ComsMasterArd to ComsMasterArd.ino
2015-11-12 Added motor testing code and the start of Accel code
2015-11-12 Pin changes
    Saves a few timers
2015-11-12 added wiring stuff
2015-11-12 Pin changes
    Corresponding library changes. Checked and still works on Santiago.
2015-11-12 Wiring progress
    Wiring diagram in Fritzing has all basic parts except DC DC converter.
    ESCs are represented by servos because they use PWM, power to them will
    be implied for now.
2015-11-14 Wiring updates
2015-11-14 Data Sheets
    This is a file with all the website links for each electronic part. Please update the sheet as new parts are added.
2015-11-14 Update pressure.cpp
    The Pressure Constructor made the arduino not do anything. After removing/adding each function in the constructor, i determined it was delay(100); that caused the problem. I have no idea why this is 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
    Changes: Removed Delay(100).
2015-11-17 Update ComsSlaveArd.ino
    Some event codes added. Still very messy
2015-11-17 Update ComsMasterArd.ino
    masterWrite now takes 1 parameter, WireEventCode, which is an int.
2015-11-20 Possibly finished the accelerometer code...
2015-11-21 Added some power board stuffs
2015-11-21 Vector Drive changes
    1) Removed the blank file that I accidentally added
    2) Added the vector drive header file
    3) Added the vector drive cpp file
2015-11-21 Integrated new motor code
2015-11-21 Ignore this
2015-11-21 Updated Coms Master And Slave
2015-11-21 ComsMasterArd Integrating in process
2015-11-21 integrated arduino
2015-11-21 SlaveCode. Pressure Sensor Functions are in
2015-11-21 Coms Master & Slave updated. the EventCodes should match now. Master can now send a Command or a Parameter to be held.
2015-11-22 Added button diagnotsics temporarily
2015-11-22 added vectorMotors files
2015-11-23 Made camera library
    I think the bit-shifting trick will work on pin assignments… otherwise
    delete three lines and uncomment the big block in camera.cpp
2016-01-09 Create pygame testing folder
2016-01-09 newfolder
2016-01-23 Update to include brownout prevention function in vector motors.cpp
    read title
2016-01-23 Added current readings
    “Voltage” spot now shows how many amps go through the whole system @48
    volts. Multiply by 4 for 12V amperage
2016-01-25 Updated readme for brownout procedure
2016-01-30 Functional UI for the UROV
2016-01-30 Make UI code for the UROV concise.
2016-01-30 Improve UI code for the UROV.
2016-02-07 Testing camera relays
    pin 13 toggles camera output relay
2016-02-16 Added Camera Switching Beta
    Works with pins 22 and 24.
2016-02-16 Added PCB directory starting point
    This has the power board. Josh will put his eagle files in the
    designated folder.
2016-02-20 ypr_testing
    ypr stuff
2016-02-20 YPR stuff
    YPR on slave should be functional
    YPR -> slave -> master -> serial3
    master will print ypr to serial3
2016-02-20 bugfixes
    coms now has properly matching data in case statement
    sampling rate to 50Hz (1/20ms)
2016-02-24 PCB changes so far
    added a few chips, not done yet though
2016-02-25 Ignore this...
2016-02-25 Don't look
2016-02-25 Power board edits
2016-02-25 Adding jumpers to select I2C or SPI
2016-02-27 Update meta files
2016-02-27 Add artificial horizon
    Basics of artificial horizon added
2016-02-27 Functional Artificial Horizon
    Artificial horizon now takes arduino's output
2016-02-27 YPR stuff
    Slave cases changes to #defines
    master sends data that luka has successfully received
    Some strange error was fixed by plugging the slave to computer, clearing
    its serial from something not sure why. This is no longer an issue.
2016-02-27 Make code concise
    Make code concise
2016-02-27 Add Normalizer
    Added normalizer and YPRraw
2016-03-04 moved a part
2016-03-04 Adding prelim sensing schematic
2016-03-04 Started Power Sensing
    Added a ADC part library, and started adding other parts to schematic
2016-03-04 Sync issues
2016-03-05 added ATTTINY84 and headers
    started working on creating MAX4574 from scratch
2016-03-05 Revisions to power board for next time
2016-03-11 Power Sensing board design
    Power sensing rough draft of PCB almost done
2016-03-12 Current sensing progress
2016-03-20 ignore
2016-03-31 Sensing board progress
2016-03-31 Updated Pins
    Named every pin on MAX485 and Multiplexer
2016-03-31 Schematic and Breadboard Update
    Organized the schematic and attached a few pins. This is my version to
    avoid any weird merges.
2016-04-02 MotorLimits & Rotations
    Added Rotations
    Cleaned up some of code for limiting motor to +-400
2016-04-02 deleted an extra line
    deleted a trash line
2016-04-02 Improved Artificial Horizon
    Improved artificial horizon, and added amps for each motor.
2016-04-02 added max4574
    took forever
2016-04-04 Added drill holes to the sensing board
2016-04-04 Moved stuff around
2016-04-09 Fixed UI connection issue
2016-04-09 Fixed bug in code
2016-04-09 Meta Files
2016-04-10 Improved Artificial Horizon
2016-04-10 Added reading heat sink temp
2016-04-10 Some vector driving fixes
2016-04-16 Comms board edits
2016-04-18 added UROV_ACCESSORIES library
    see above
2016-04-18 justSomePins
2016-04-18 Crashes less often...
2016-04-22 Vector code V1 works
2016-04-23 Vector code perfected, artificial horizon works
2016-04-23 Created low pass filter for sensor data
    Created low pass filter for sensor data
2016-04-23 SM i think complete but untested
2016-04-23 a little cleaning
2016-04-23 Improved efficiency and and improved A.H.
    Improved efficiency by deleting unnecessary fucntion and importing less
    stuff and improved A.H. by adding 5 point filter.
2016-04-23 To be tested monday ish
    stepper motor: master can send a preprogrammed 1.8degrees and direction,
    or send a custom distance and direction. slave now able to receive
    parameters in addition to commands. Untested.
2016-04-26 kjhkhkhj
2016-04-27 Added camera updates
2016-05-07 updated board
    rearranged board configuration, added wago screw clamps
2016-05-15 Made berbers for Sensing and power bus boards
2016-05-16 Accessory Board possible edits
    Unless Josh had better changes
2016-05-26 Inproments to the UI
    Added half power mode, improved AH filter, organized code and added
    comments.
2016-05-28 Deleted unused varibles
    Deleted unused varibles
2016-05-28 Removed Labels on Arduino's communication
    Removed Labels on Arduino's communication
2016-06-05 Started work on current sensing
    Chip under test: LTC 1856
    Should interface with AtTiny when done.
2016-06-11 Current sense branch start
2016-06-11 Preliminary Current Sensing Driver
2016-06-12 More updates
    Tested with Luca’s most recent interface. Still debugging various motor
    readings
2016-06-17 Merges resolved
2016-06-17 Improved UI
    Added crash reports and the ability to receive motor info.
2016-06-23 Cameras Fixed?
2016-06-23 Rewriting the relay camera switching code
2016-06-23 BNO commented out
2016-09-12 Small changes
    Just comiting because i am going to have my computer repaired and I
    might lose my files.

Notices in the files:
parts and their libraries:
SparkFun-Connectors: Licensing: Creative Commons ShareAlike 4.0 International - https://creativecommons.org/licenses/by-sa/4.0
